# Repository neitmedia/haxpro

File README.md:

# **H**igh **A**ltitude E**X**ploration **Pro**be II

*Barometric Pressure Sensor:* BMP180
haxpro
*Humidity and Temperature Sensor:* Si7021

*IMU 9DoF:* MPU-9250

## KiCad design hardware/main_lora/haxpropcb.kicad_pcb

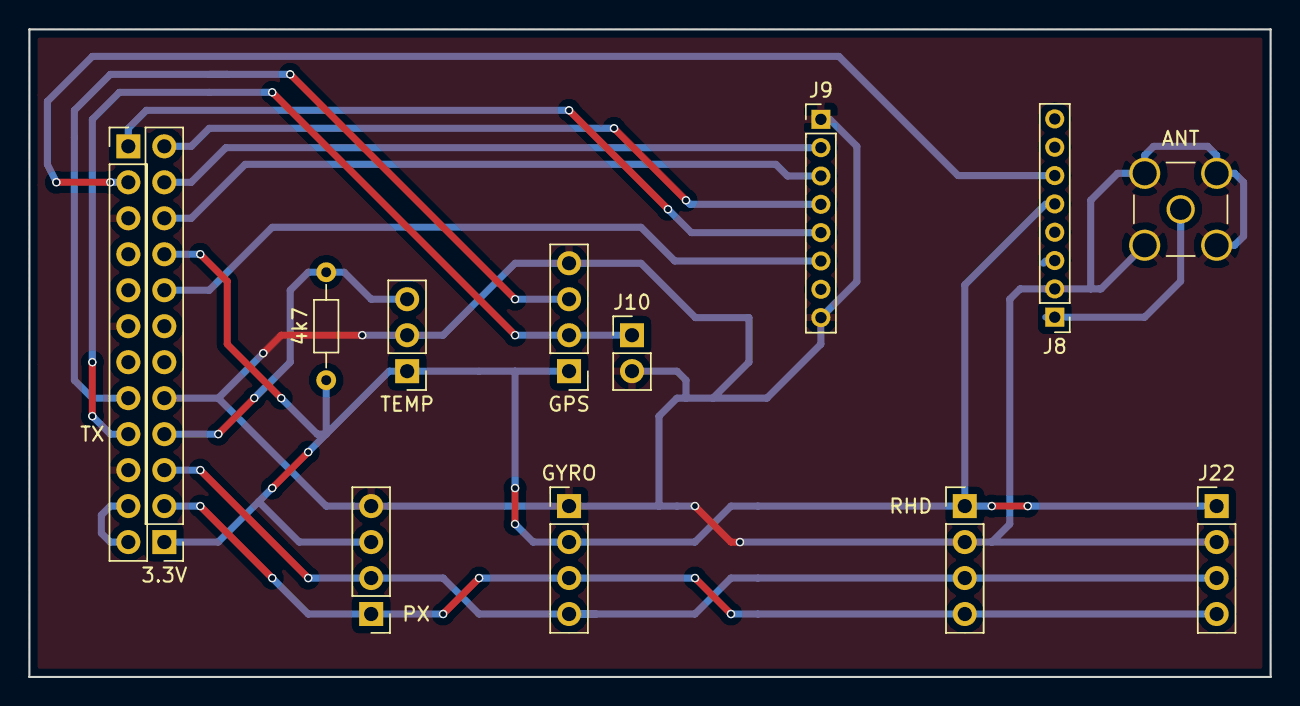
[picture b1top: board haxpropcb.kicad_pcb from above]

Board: 2 copper layers, 87.6 x 45.7 mm, 13 parts (0 on the bottom side), 15 nets.

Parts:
3.3V: Conn_01x12_Female; Socket_Strip_Straight_1x12_Pitch2.54mm
4k7: 4k7; R_Axial_DIN0204_L3.6mm_D1.6mm_P7.62mm_Horizontal
ANT: Conn_Coaxial; SMA_THT_Jack_Straight
GPS: Conn_01x04_Female; Socket_Strip_Straight_1x04_Pitch2.54mm
GYRO: Conn_01x04_Female; Socket_Strip_Straight_1x04_Pitch2.54mm
J8, J9: Conn_01x08_Female; Socket_Strip_Straight_1x08_Pitch2.00mm
J10: Conn_01x02_Female; Socket_Strip_Straight_1x02_Pitch2.54mm
J22: Conn_01x04_Female; Socket_Strip_Straight_1x04_Pitch2.54mm
PX: Conn_01x04_Female; Socket_Strip_Straight_1x04_Pitch2.54mm
RHD: Conn_01x04_Female; Socket_Strip_Straight_1x04_Pitch2.54mm
TEMP: Conn_01x03_Female; Socket_Strip_Straight_1x03_Pitch2.54mm
TX: Conn_01x12_Female; Socket_Strip_Straight_1x12_Pitch2.54mm

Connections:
/+3,3V: 3.3V.1, 3.3V.9, 4k7.1, GPS.1, GYRO.2, J8.5, J22.1, PX.3, RHD.1, TEMP.1
/+5V: TX.11, TX.12
/ANT: ANT.1, J8.1
/BCM4: 3.3V.4, 4k7.2, TEMP.3
/BCM22: 3.3V.8, J9.6
/BCM25: J8.6, TX.2
/CS0: J9.5, TX.1
/MISO: 3.3V.11, J9.2
/MOSI: 3.3V.10, J9.3
/RX: GPS.2, J10.1, TX.9
/SCL: 3.3V.3, GYRO.4, J22.3, PX.2, RHD.3
/SCLK: 3.3V.12, J9.4
/SDA: 3.3V.2, GYRO.3, J22.4, PX.1, RHD.4
/TX: GPS.3, TX.8
GND: 3.3V.5, ANT.2, GPS.4, GYRO.1, J8.2, J9.1, J9.8, J10.2, J22.2, PX.4, RHD.2, TEMP.2, TX.3, TX.6, TX.10

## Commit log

2017-10-07 added cables
2017-10-07 deleted old file
2017-10-07 Genehmigugnsstuff
2017-10-07 renaming files
2017-11-04 Add files via upload
    BMP180 ersetzt durch MPL3115A2
2018-01-06 intro bits for video
2018-02-26 new intro video
2018-03-15 new files
2018-03-15 add presentation
2018-03-15 update presentation
2018-03-15 spelling
2018-03-16 Removed old files
2018-03-16 scripts
2018-03-16 added hardware design
2018-03-16 added rtty beta schematics
2018-03-16 added software infos
2018-03-16 new intro
2018-03-16 boden video
2018-03-16 fix intro and mdr
2018-03-18 added sht21 library
2018-03-19 add slide
2018-03-19 upload scripts
2018-03-20 update slides
2018-03-24 added telemetry scripts
2018-04-01 updated rtty hardware schematics
